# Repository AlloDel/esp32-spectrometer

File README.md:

# esp32-spectrometer
A sample control board for a spectrometer based on esp32 microcontroller

Schematic and images of a 3D render of the board

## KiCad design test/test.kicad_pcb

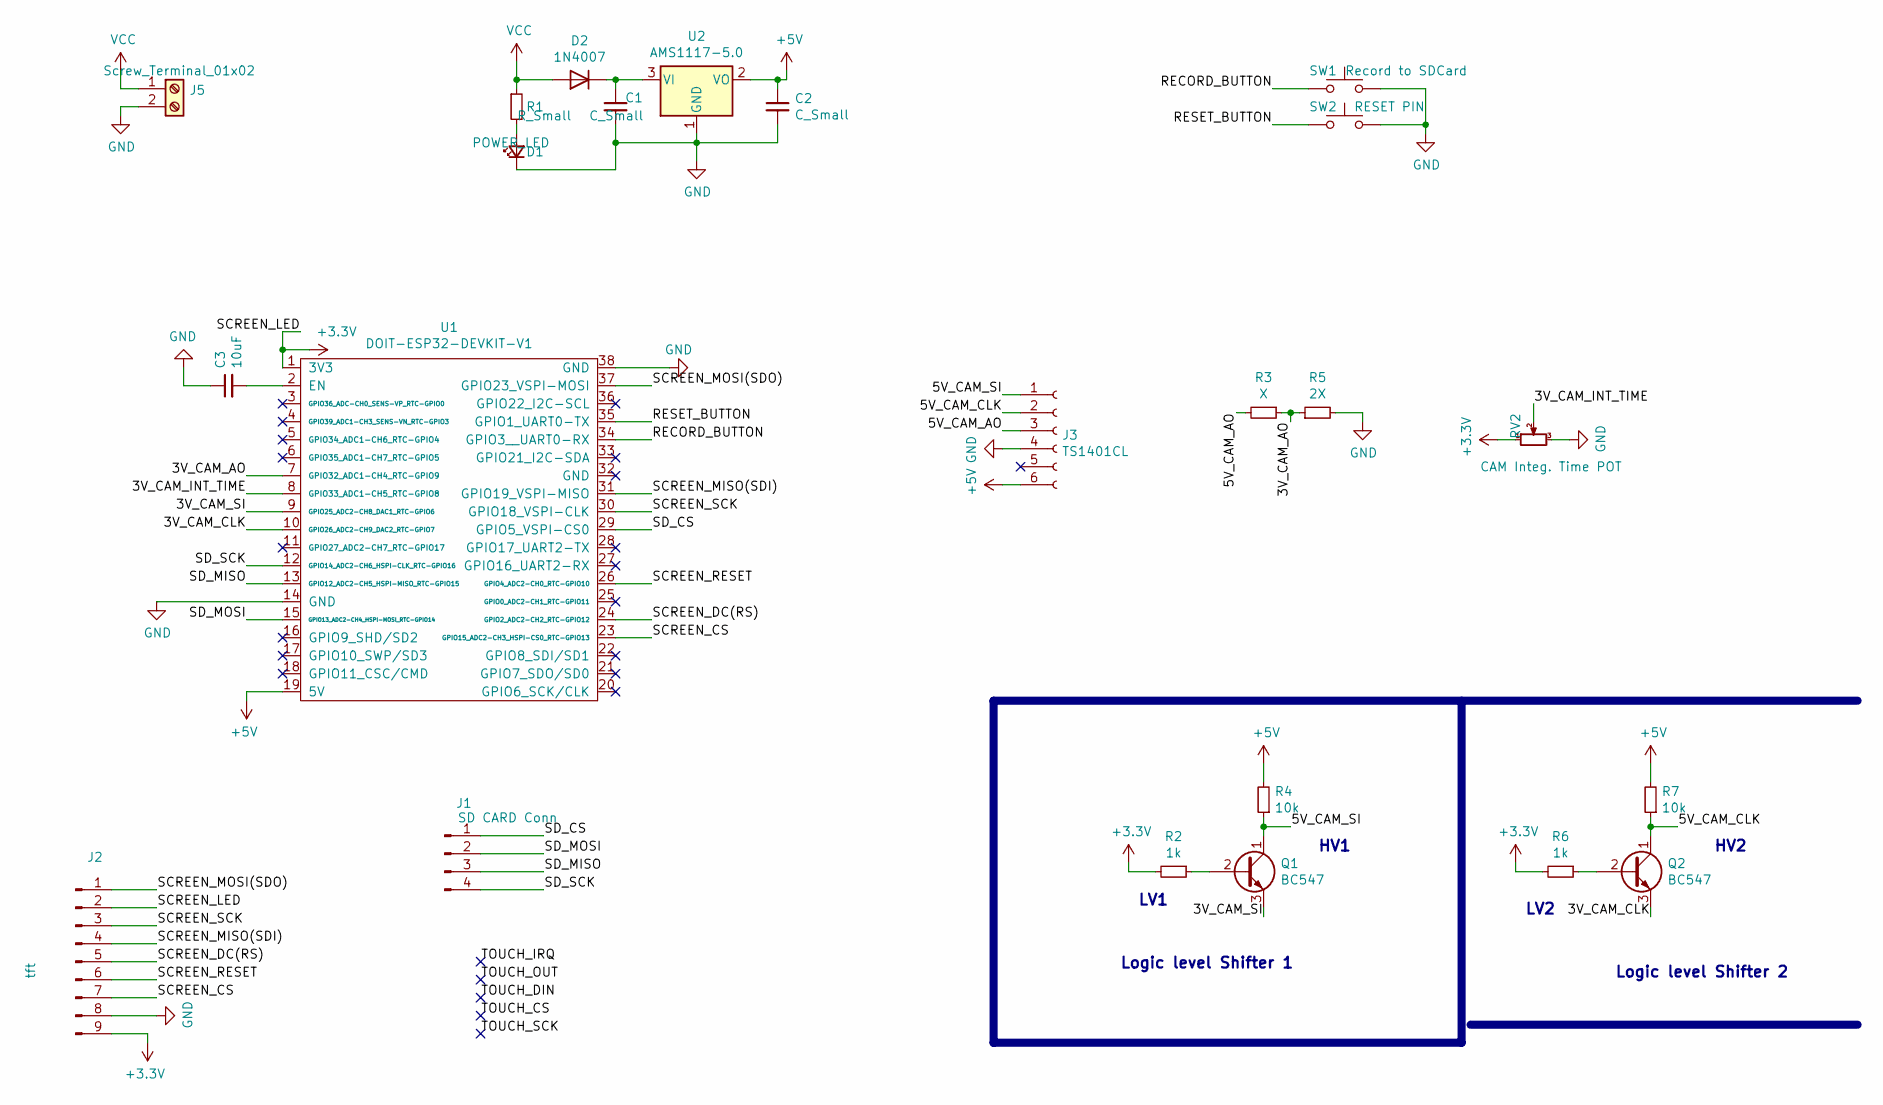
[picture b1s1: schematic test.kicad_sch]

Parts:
C1, C2: C_Small; C_Radial_D6.3mm_H7.0mm_P2.50mm
C3: 10uF; C_Radial_D6.3mm_H7.0mm_P2.50mm
D1: POWER_LED; LED_D5.0mm_Clear
D2: 1N4007; D_DO-41_SOD81_P10.16mm_Horizontal
J1: SD CARD Conn; PinSocket_1x04_P2.54mm_Vertical
J2: tft; PinHeader_1x09_P2.54mm_Vertical
J3: TS1401CL; PinSocket_1x06_P2.54mm_Vertical
J5: Screw_Terminal_01x02; TerminalBlock_bornier-2_P5.08mm
Q1, Q2: BC547; TO-92_Wide
R1: R_Small; R_Axial_DIN0411_L9.9mm_D3.6mm_P12.70mm_Horizontal
R2, R6: 1k; R_Axial_DIN0414_L11.9mm_D4.5mm_P7.62mm_Vertical
R3: X; R_Axial_DIN0414_L11.9mm_D4.5mm_P7.62mm_Vertical
R4, R7: 10k; R_Axial_DIN0414_L11.9mm_D4.5mm_P7.62mm_Vertical
R5: 2X; R_Axial_DIN0414_L11.9mm_D4.5mm_P15.24mm_Horizontal
RV2: CAM Integ. Time POT; Potentiometer_Runtron_RM-065_Vertical
SW1: Record to SDCard; SW_PUSH_6mm_H13mm
SW2: RESET PIN; SW_PUSH_6mm_H13mm
U1: DOIT-ESP32-DEVKIT-V1; ESP32-DOIT-DEVKIT-36PIN
U2: AMS1117-5.0; SOT-223-3_TabPin2

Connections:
+3V3: J2.2, J2.9, R2.2, R6.2, RV2.1, U1.1 (3V3)
+5V: C2.1, J3.6, R4.2, R7.2, U1.19 (5V), U2.2 (VO)
/3V_CAM_AO: R3.1, R5.1, U1.7 (GPIO32_ADC1-CH4_RTC-GPIO9)
/3V_CAM_CLK: Q2.3 (E), U1.10 (GPIO26_ADC2-CH9_DAC2_RTC-GPIO7)
/3V_CAM_INT_TIME: RV2.2, U1.8 (GPIO33_ADC1-CH5_RTC-GPIO8)
/3V_CAM_SI: Q1.3 (E), U1.9 (GPIO25_ADC2-CH8_DAC1_RTC-GPIO6)
/5V_CAM_AO: J3.3, R3.2
/5V_CAM_CLK: J3.2, Q2.1 (C), R7.1
/5V_CAM_SI: J3.1, Q1.1 (C), R4.1
/RECORD_BUTTON: SW1.1, U1.34 (GPIO3__UART0-RX)
/RESET_BUTTON: SW2.1, U1.35 (GPIO1_UART0-TX)
/SCREEN_CS: J2.7, U1.23 (GPIO15_ADC2-CH3_HSPI-CS0_RTC-GPIO13)
/SCREEN_DC(RS): J2.5, U1.24 (GPIO2_ADC2-CH2_RTC-GPIO12)
/SCREEN_MISO(SDI): J2.4, U1.31 (GPIO19_VSPI-MISO)
/SCREEN_MOSI(SDO): J2.1, U1.37 (GPIO23_VSPI-MOSI)
/SCREEN_RESET: J2.6, U1.26 (GPIO4_ADC2-CH0_RTC-GPIO10)
/SCREEN_SCK: J2.3, U1.30 (GPIO18_VSPI-CLK)
/SD_CS: J1.1, U1.29 (GPIO5_VSPI-CS0)
/SD_MISO: J1.3, U1.13 (GPIO12_ADC2-CH5_HSPI-MISO_RTC-GPIO15)
/SD_MOSI: J1.2, U1.15 (GPIO13_ADC2-CH4_HSPI-MOSI_RTC-GPIO14)
/SD_SCK: J1.4, U1.12 (GPIO14_ADC2-CH6_HSPI-CLK_RTC-GPIO16)
GND: C1.2, C2.2, C3.1, D1.1 (K), J2.8, J3.4, J5.2, R5.2, RV2.3, SW1.2, SW2.2, U1.14 (GND), U1.38 (GND), U2.1 (GND)
unnamed: C1.1, D2.1 (K), U2.3 (VI)
unnamed: C3.2, U1.2 (EN)
unnamed: D1.2 (A), R1.2
unnamed: Q1.2 (B), R2.1
unnamed: Q2.2 (B), R6.1
VCC: D2.2 (A), J5.1, R1.1

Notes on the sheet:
HV2
LV1
Logic level Shifter 2
LV2
HV1
Logic level Shifter 1

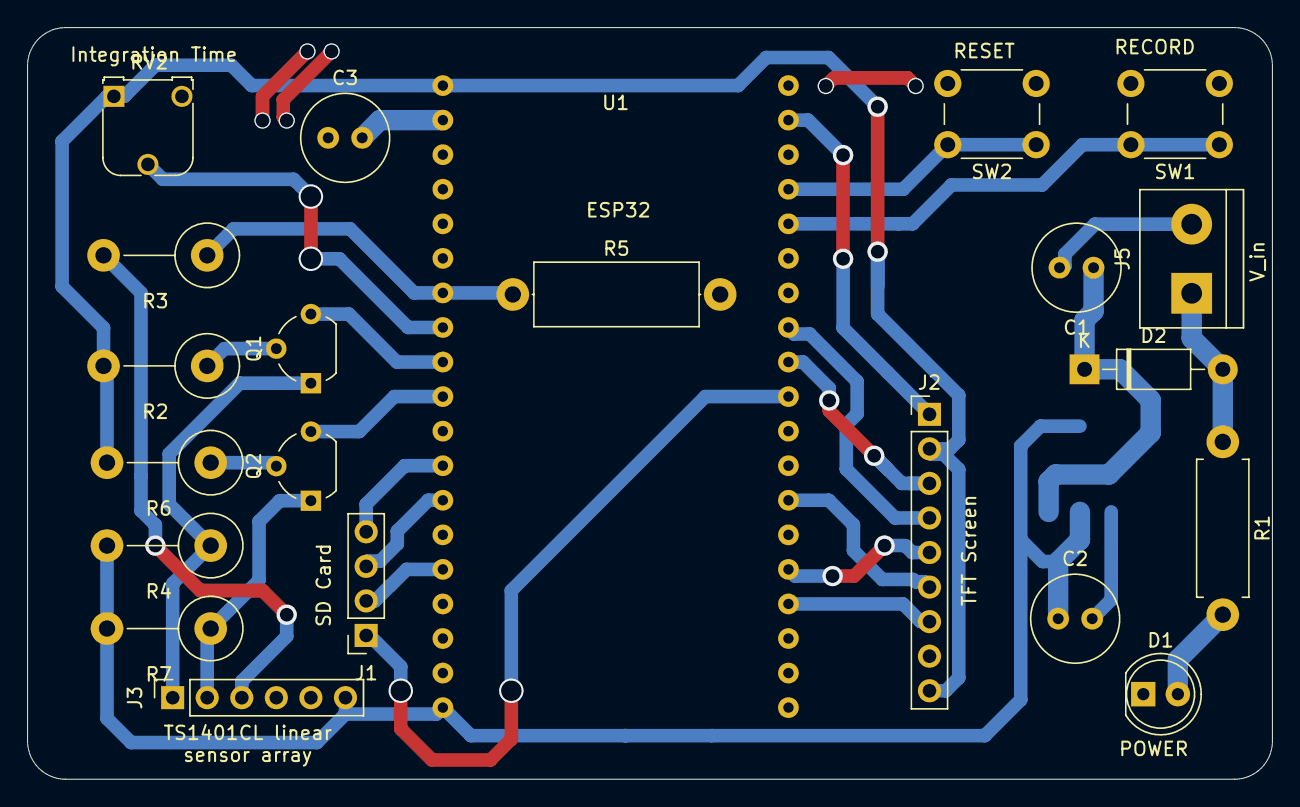
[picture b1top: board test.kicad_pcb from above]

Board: 2 copper layers, 91.5 x 55.2 mm, 23 parts (1 on the bottom side), 28 nets.
